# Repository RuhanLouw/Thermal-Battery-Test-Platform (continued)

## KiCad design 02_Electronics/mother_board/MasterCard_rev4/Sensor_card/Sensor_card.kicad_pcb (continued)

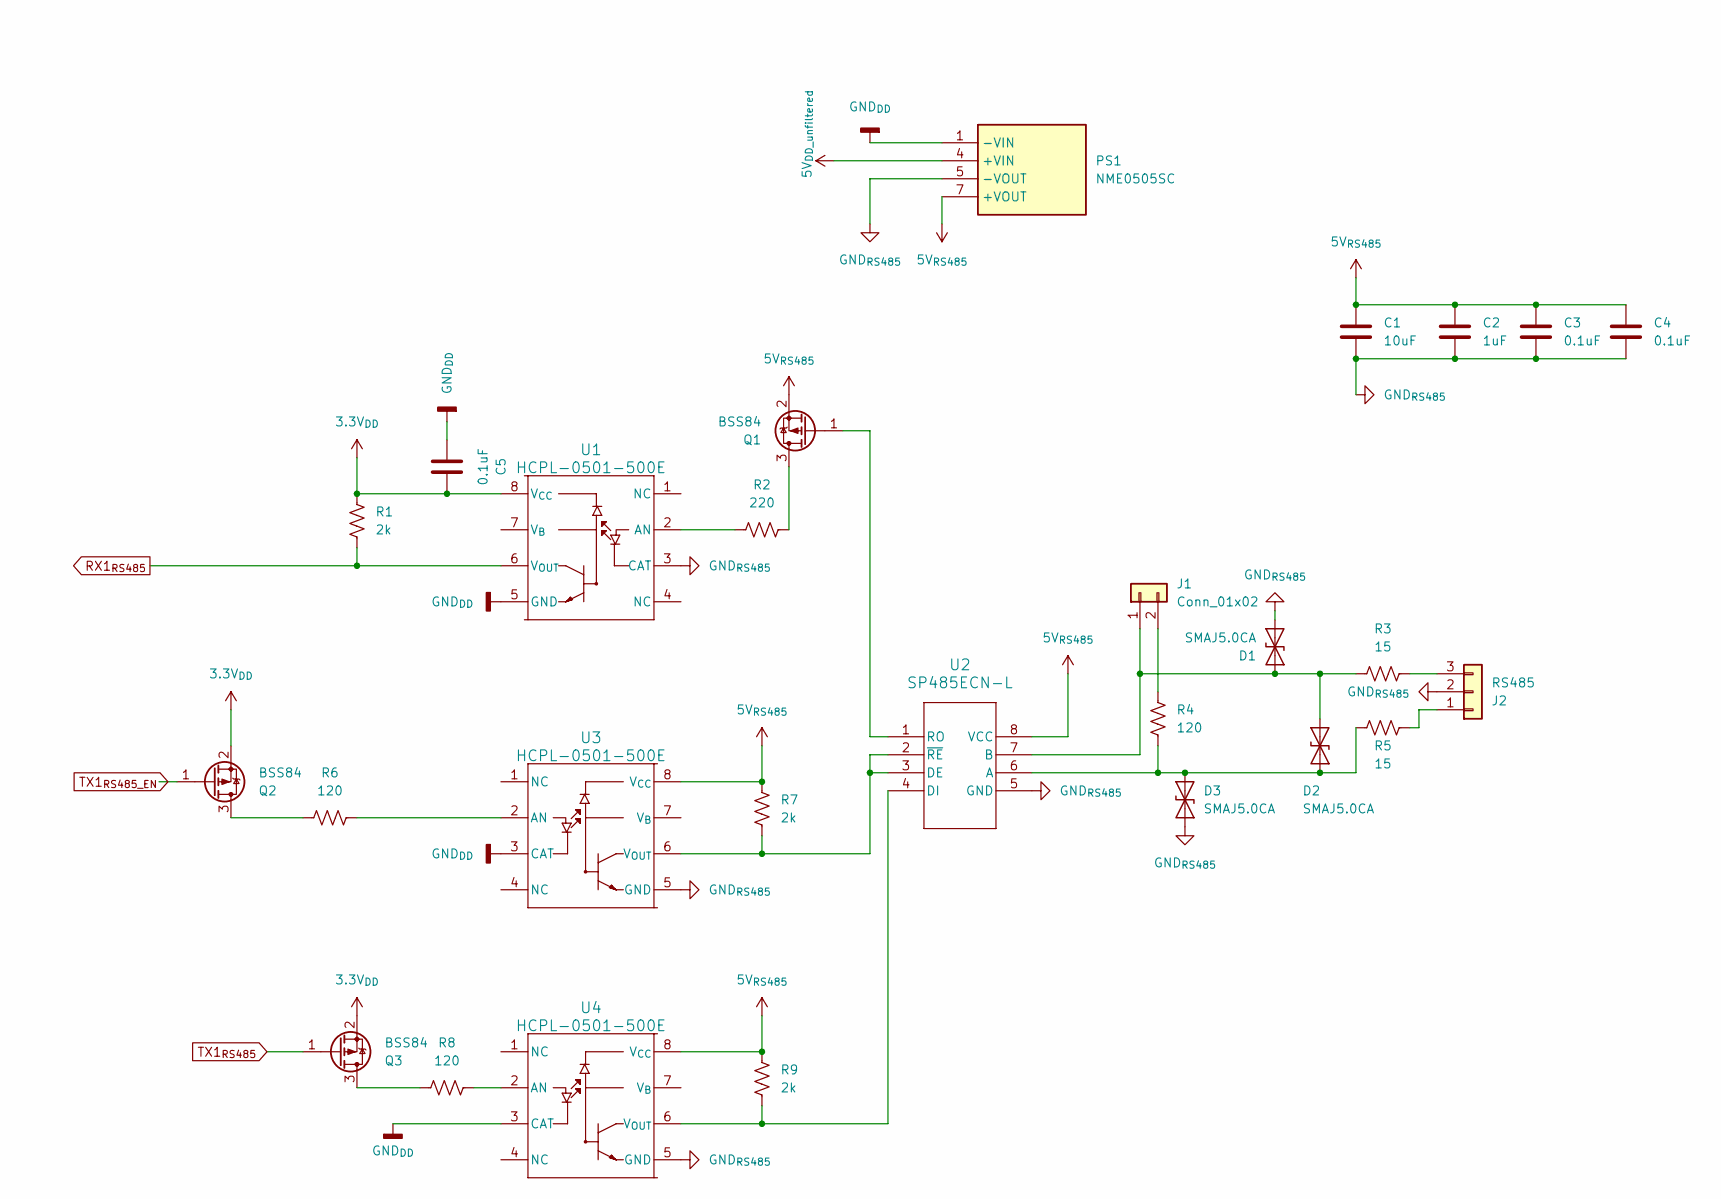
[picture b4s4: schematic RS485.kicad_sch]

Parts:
C1: 10uF; C_0805_2012Metric
C2: 1uF; C_0603_1608Metric
C3, C4, C5: 0.1uF; C_0603_1608Metric
D1, D2, D3: SMAJ5.0CA; D_SMA
J1: Conn_01x02; PinHeader_1x02_P2.54mm_Vertical
J2: RS485; TE_282857-3_screw
PS1: NME0505SC; Mouser Part Number 580-NME0505SC
Q1, Q2, Q3: BSS84; SOT-23
R1, R7, R9: 2k; R_0603_1608Metric
R2: 220; R_0603_1608Metric
R3, R5: 15; R_1206_3216Metric
R4, R6, R8: 120; R_0603_1608Metric
U1, U3, U4: HCPL-0501-500E; SO8_HCPL-0501-500_BRA
U2: SP485ECN-L; NSOIC-8

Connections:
3.3V_{DD}: C5.2, Q2.2 (S), Q3.2 (S), R1.2, U1.8 (V_{CC}); also elsewhere on the board
5V_{DD_unfiltered}: PS1.4 (+VIN); also elsewhere on the board
5V_{RS485}: C1.1, C2.1, C3.1, C4.1, PS1.7 (+VOUT), Q1.2 (S), R7.2, R9.2, U2.8 (VCC), U3.8 (V_{CC}), U4.8 (V_{CC})
GND_{DD}: C5.1, PS1.1 (-VIN), U1.5 (GND), U3.3 (CAT), U4.3 (CAT); also elsewhere on the board
GND_{RS485}: C1.2, C2.2, C3.2, C4.2, D1.1 (A1), D3.1 (A1), J2.2, PS1.5 (-VOUT), U1.3 (CAT), U2.5 (GND), U3.5 (GND), U4.5 (GND)
unnamed: D1.2 (A2), D2.1 (A1), J1.1, R3.1, U2.7 (B)
unnamed: D2.2 (A2), D3.2 (A2), R4.2, R5.1, U2.6 (A)
unnamed: J1.2, R4.1
unnamed: J2.1, R5.2
unnamed: J2.3, R3.2
unnamed: Q1.3 (D), R2.1
unnamed: Q1.1 (G), U2.1 (RO)
unnamed: Q2.3 (D), R6.1
unnamed: Q3.3 (D), R8.1
unnamed: R2.2, U1.2 (AN)
unnamed: R7.1, U2.2 (~RE), U2.3 (DE), U3.6 (V_{OUT})
unnamed: R9.1, U2.4 (DI), U4.6 (V_{OUT})
unnamed: R6.2, U3.2 (AN)
unnamed: R8.2, U4.2 (AN)
RX1_{RS485}: R1.1, U1.6 (V_{OUT}); also elsewhere on the board
TX1_{RS485_EN}: Q2.1 (G); also elsewhere on the board
TX1_{RS485}: Q3.1 (G); also elsewhere on the board

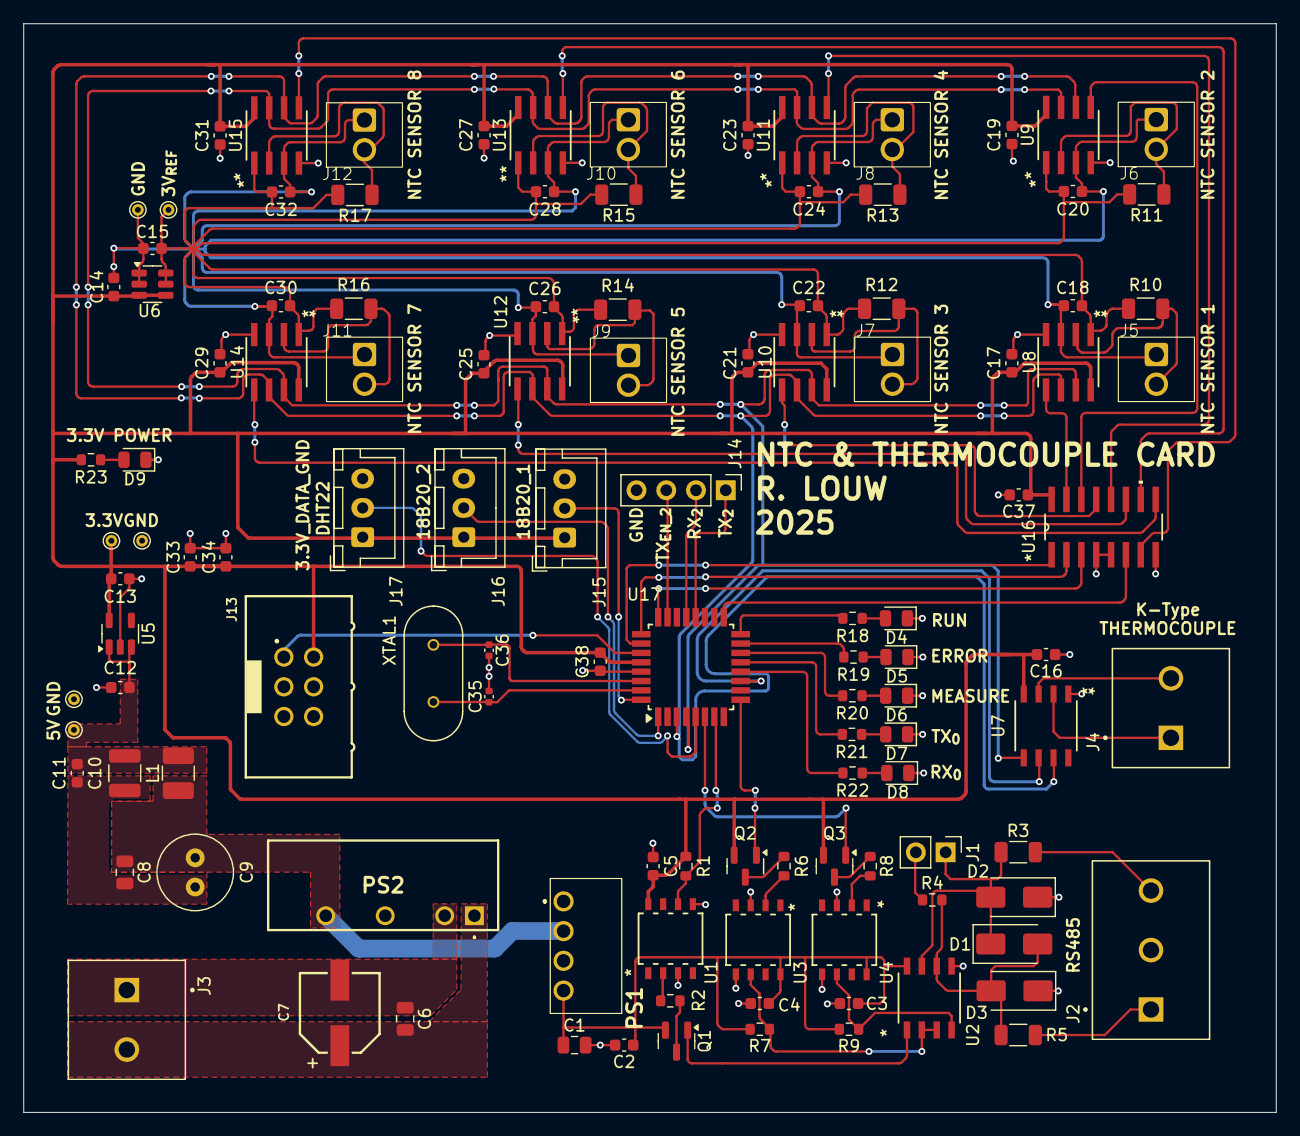
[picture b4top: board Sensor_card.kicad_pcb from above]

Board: 2 copper layers, 107.0 x 93.0 mm, 113 parts (1 on the bottom side), 88 nets.

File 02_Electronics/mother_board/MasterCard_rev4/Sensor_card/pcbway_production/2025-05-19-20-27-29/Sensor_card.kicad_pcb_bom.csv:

Designator,Quantity,Value,Footprint,Package,MPN,DNP,Mount_Type,Description,Sim.Pins,Height,Mouser Part Number,Mouser Price/Stock,Manufacturer_Name,PARTREV,STANDARD,MANUFACTURER
"C1, C6, C8",3,10uF,C_0805_2012Metric,,,,smt,10 µF ±10% 10V Ceramic Capacitor X7R 0805 (2012 Metric),,,,,,,,
C10,1,22uF,C_1210_3225Metric,,,,smt,CAP CER 22UF 16V X7R 1210,,,,,,,,
"C11, C14, C2, C33",4,1uF,C_0603_1608Metric,,,,smt,[C33]CAP CER 1UF 25V X7R 0603; [C2]CAP CER 1UF 10V X7R 0603,,,,,,,,
"C12, C13, C15",3,2.2uF,C_0603_1608Metric,,,,smt,CAP CER 2.2UF 25V X5R 0603,,,,,,,,
"C16, C17, C18, C19, C20, C21, C22, C23, C24, C25, C26, C27, C28, C29, C3, C30, C31, C32, C37, C38, C4, C5",22,0.1uF,C_0603_1608Metric,,,,smt,"[C37,C38]0.1 µF ±10% 50V Ceramic Capacitor X7R 0603 (1608 Metric); [C4,C5]Unpolarized capacitor",,,,,,,,
C34,1,10n,C_0603_1608Metric,,,,smt,Unpolarized capacitor,,,,,,,,
"C35, C36",2,18pF,C_0402_1005Metric,,,,smt,CAP CER 18PF 50V C0G/NP0 0402,,,,,,,,
C7,1,47uF,WCAP-ASLI_6.3X5.5_DXL_47uF,,,,smt,"47 µF 35 V Aluminum Electrolytic Capacitors Radial, Can - SMD 2000 Hrs @ 105°C",,,,,,,,
C9,1,100uF,C_Radial_D6.3mm_H11.0mm_P2.50mm,,,,tht,CAP ALUM 100UF 20% 35V RADIAL TH KEMET,,,,,,,,
"D1, D2, D3",3,SMAJ5.0CA,D_SMA,,,,smt,"400W bidirectional Transient Voltage Suppressor, 5.0Vr, SMA(DO-214AC)",,,,,,,,
"D4, D5, D6, D7, D8, D9",6,LED,LED_0805_2012Metric,,,,smt,LED GREEN CLEAR 0805 SMD,1=K 2=A,,,,,,,
J1,1,Conn_01x02,PinHeader_1x02_P2.54mm_Vertical,,,,tht,"Generic connector, single row, 01x02, script generated (kicad-library-utils/schlib/autogen/connector/)",,,,,,,,
"J10, J11, J12, J5, J6, J7, J8, J9",8,Screw_Terminal_01x02,TERM BLOCK 2P HORIZON 2.54MM PCB,,,,tht,"Generic screw terminal, single row, 01x02, script generated (kicad-library-utils/schlib/autogen/connector/)",,,,,,,,
J13,1,Conn_02x03_Top_Bottom,61200621621,,,,tht,"Generic connector, double row, 02x03, top/bottom pin numbering scheme (row 1: 1...pins_per_row, row2: pins_per_row+1 ... num_pins), script generated (kicad-library-utils/schlib/autogen/connector/)",,,,,,,,
J14,1,Conn_01x03,PinHeader_1x03_P2.54mm_Vertical,,,,tht,"Generic connector, single row, 01x03, script generated (kicad-library-utils/schlib/autogen/connector/)",,,,,,,,
"J15, J16, J17",3,Conn_01x03,JST_XH_B3B-XH-A_1x03_P2.50mm_Vertical,,,,tht,"Generic connector, single row, 01x03, script generated (kicad-library-utils/schlib/autogen/connector/)",,,,,,,,
J2,1,RS485,TE_282857-3_screw,,,,tht,"Generic connector, single row, 01x03, script generated (kicad-library-utils/schlib/autogen/connector/)",,,,,,,,
"J3, J4",2,Screw_Terminal_01x02,TE_282857-2_screw,,,,tht,"[J3]2 Position Wire to Board Terminal Block Horizontal with Board 0.200"" (5.08mm) Through Hole; [J4]Generic screw terminal, single row, 01x02, script generated (kicad-library-utils/schlib/autogen/connector/)",,,,,,,,
L1,1,4.7uH,L_1210_3225Metric_Pad1.42x2.65mm_HandSolder_cad,,,,smt,4.7 µH Unshielded Wirewound Inductor 800 mA 190mOhm Max 1210 (3225 Metric),,,,,,,,
PS1,1,NME0505SC,NME0505SC,,NME0505SC,,tht,"Murata Power Solutions NME 1W Isolated DC-DC Converter Through Hole, Vin 4.5  5.5 V dc, Vout 5V dc",,10.25,580-NME0505SC,https://www.mouser.co.uk/ProductDetail/Murata-Power-Solution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,Murata Electronics,,,
PS2,1,NMG1205SC,NMG1205SC,,,,tht,Isolated DC/DC Converters - Through Hole 2W TH 2W 12-5V SIP DC/DC,,,,,,,,
"Q1, Q2, Q3",3,BSS84,SOT-23,,,,smt,"-0.13A Id, -50V Vds, P-Channel MOSFET, SOT-23",,,,,,,,
"R1, R7, R9",3,2k,R_0603_1608Metric,,,,smt,"Resistor, US symbol",,,,,,,,
"R10, R11, R12, R13, R14, R15, R16, R17",8,10k,R_1206_3216Metric,,,,smt,"10 kOhms ±0.01% 0.25W, 1/4W Chip Resistor 1206 (3216 Metric) Automotive AEC-Q200 Thin Film",,,,,,,,
"R18, R19, R20, R21, R22, R23",6,75,R_0603_1608Metric,,,,smt,RES SMD 75 OHM 1% 1/10W 0603,,,,,,,,
R2,1,220,R_0603_1608Metric,,,,smt,"Resistor, US symbol",,,,,,,,
"R3, R5",2,15,R_1206_3216Metric,,,,smt,"Resistor, US symbol",,,,,,,,
"R4, R6, R8",3,120,R_0603_1608Metric,,,,smt,"Resistor, US symbol",,,,,,,,
"Star_Point1, Star_Point2",2,8,STARPOINT 9 ROUND PAD,,,,smt,,,,,,,,,
TIE1,1,~,Star_Point_3,,,,smt,,,,,,,,,
"U1, U3, U4",3,HCPL-0501-500E,SO8_HCPL-0501-500_BRA,,,,smt,,,,,,,,,
"U10, U11, U12, U13, U14, U15, U8, U9",8,MCP3201,SOIC8-N_MC_MCH,,,,smt,"2.7V 12-Bit A/D Converter with SPI™ Serial Interface, PDIP-8/SOIC-8/MSOP-8/TSSOP-8",,,,,,,,
U16,1,SN74HC138DR,SN74HC138DR,,,,smt,Decoder/Demultiplexer 1 x 3:8 16-SOIC,,,,,,,,
U17,1,AVR128DB32x-xPT,TQFP-32_7x7mm_P0.8mm,,,,smt,"24MHz, 128kB Flash, 16kB SRAM, EEPROM with Op Amps and Multi-Voltage I/O, TQFP-32",,,,,,,,
U2,1,SP485ECN-L,NSOIC-8,,,,smt,RS485,,,,,,,,
U5,1,LP5907MFX-3.3,SOT-23-5,,,,smt,"250-mA Ultra-Low-Noise Low-IQ LDO, 3.3V, SOT-23",,,,,,,,
U6,1,REF3430IDBVR,SOT-23-6,,,,smt,Series Voltage Reference IC Fixed 3V V ±0.05% 10 mA SOT-23-6,,,,,,,,
U7,1,MAX31855KASA+T,21-0041B_8_MXM,,,,smt,,,,,,,,,
XTAL1,1,ABL-16.000MHZ-B2,XTAL_HC49P488W46L1150T500H350,,,,tht,16 MHz ±20ppm Crystal 18pF 40 Ohms HC-49/US,,,,,,03.27.2018,IPC-7351B,Abracon

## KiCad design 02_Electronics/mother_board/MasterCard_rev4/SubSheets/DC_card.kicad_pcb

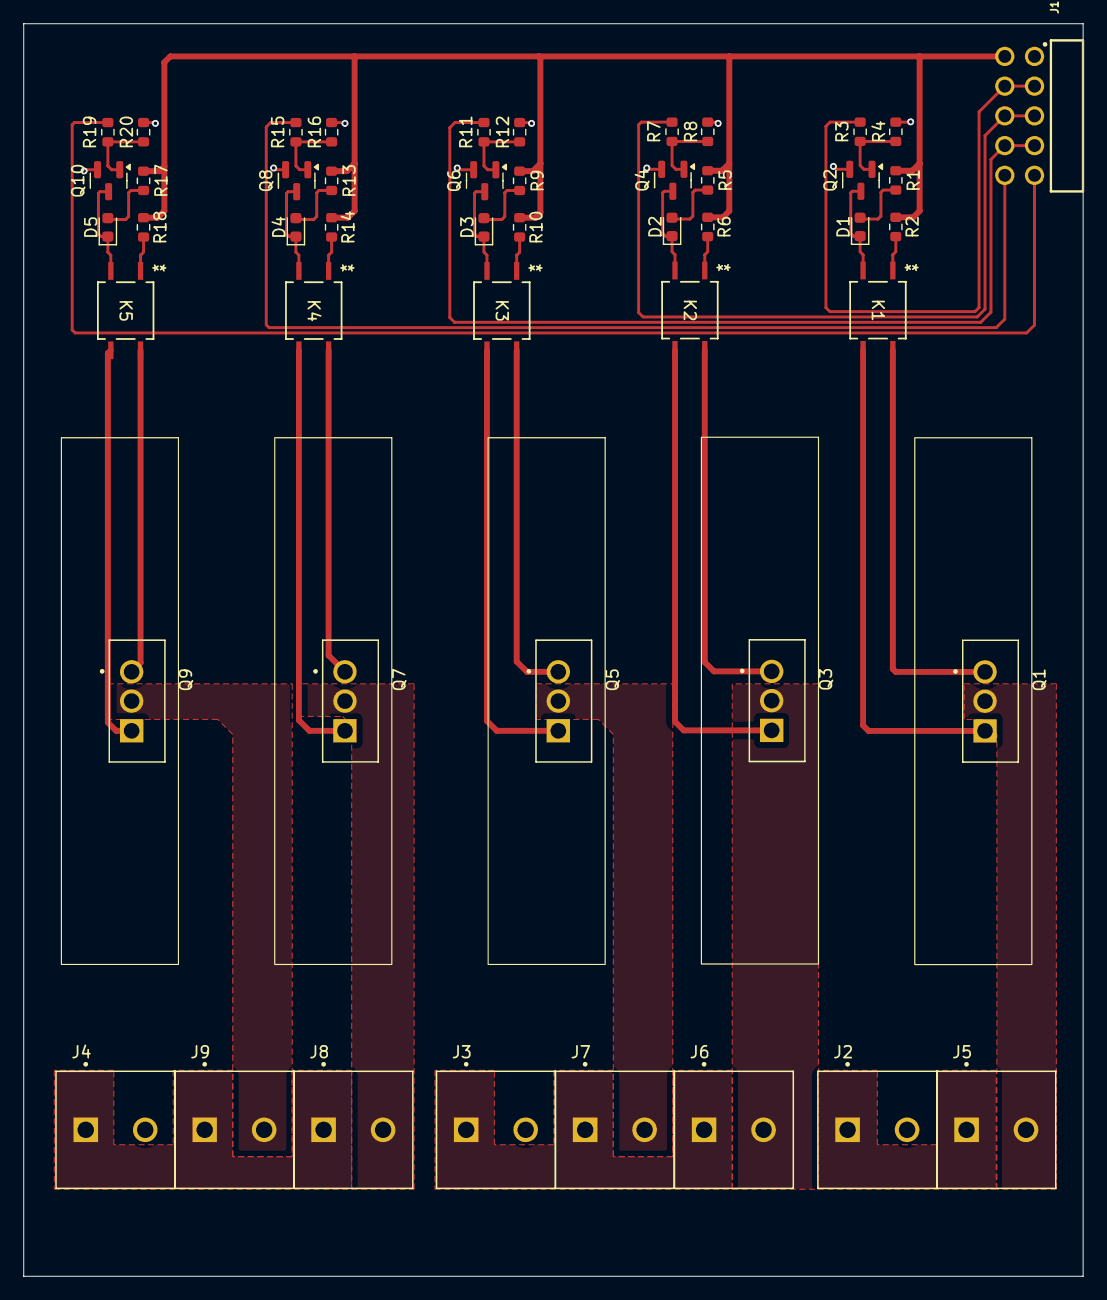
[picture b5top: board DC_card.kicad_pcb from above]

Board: 2 copper layers, 90.5 x 107.0 mm, 49 parts (0 on the bottom side), 43 nets.

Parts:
D1, D2, D3, D4, D5: LED; D_0603_1608Metric
J1: CONN HEADER R/A 10POS 2.54MM; CONN HEADER RA 10POS 2.54MM
J2, J3, J4: Own 12 Supply; TE_282857-2_screw
J5, J6, J7, J8, J9: DC_Compressor_MAIN; TE_282857-2_screw
K1, K2, K3, K4, K5: APV1121S; SOP4PIN_PAN-M
Q1, Q3, Q5, Q7, Q9: IRFB7545PBF; v2008b_IRFB7545PBF
Q2, Q4, Q6, Q8, Q10: BSS138L; SOT-23
R1, R5, R9, R13, R17: 142; R_0603_1608Metric
R2, R6, R10, R14, R18: 187; R_0603_1608Metric
R3, R7, R11, R15, R19: 300; R_0603_1608Metric
R4, R8, R12, R16, R20: 10k; R_0603_1608Metric

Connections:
5V_{DD}: J1.2, R1.2, R2.1, R5.2, R6.1, R9.2, R10.1, R13.2, R14.1, R17.2, R18.1
12V_{CC_comp}: J2.1, J5.1
12V_{CC_fans}: J4.1, J8.1, J9.1
12V_{CC_hbed}: J3.1, J6.1, J7.1
Compressor_MAIN: J1.3, J1.4, R3.1
Evaporator_FAN: J1.10, R15.1
GND_{CC_comp}: J2.2, K1.3, Q1.3 (S)
GND_{CC_fans}: J4.2, K4.3, K5.3, Q7.3 (S), Q9.3 (S)
GND_{CC_hbed}: J3.2, K2.3, K3.3, Q3.3 (S), Q5.3 (S)
GND_{DD}: J1.1, Q2.2 (S), Q4.2 (S), Q6.2 (S), Q8.2 (S), Q10.2 (S), R4.2, R8.2, R12.2, R16.2, R20.2
HeatBed_1: J1.5, J1.6, R7.1
HeatBed_2: J1.7, J1.8, R11.1
HeatBed_FAN: J1.9, R19.1
unnamed: D1.2 (A), R1.1
unnamed: D1.1 (K), K1.2, Q2.3 (D)
unnamed: D2.2 (A), R5.1
unnamed: D2.1 (K), K2.2, Q4.3 (D)
unnamed: D3.2 (A), R9.1
unnamed: D3.1 (K), K3.2, Q6.3 (D)
unnamed: D4.2 (A), R13.1
unnamed: D4.1 (K), K4.2, Q8.3 (D)
unnamed: D5.2 (A), R17.1
unnamed: D5.1 (K), K5.2, Q10.3 (D)
unnamed: J5.2, Q1.1 (D)
unnamed: J6.2, Q3.1 (D)
unnamed: J7.2, Q5.1 (D)
unnamed: J8.2, Q7.1 (D)
unnamed: J9.2, Q9.1 (D)
unnamed: K1.1, R2.2
unnamed: K2.1, R6.2
unnamed: K3.1, R10.2
unnamed: K4.1, R14.2
unnamed: K5.1, R18.2
unnamed: K1.4, Q1.2 (G)
unnamed: Q2.1 (G), R3.2, R4.1
unnamed: K2.4, Q3.2 (G)
unnamed: Q4.1 (G), R7.2, R8.1
unnamed: K3.4, Q5.2 (G)
unnamed: Q6.1 (G), R11.2, R12.1
unnamed: K4.4, Q7.2 (G)
unnamed: Q8.1 (G), R15.2, R16.1
unnamed: K5.4, Q9.2 (G)
unnamed: Q10.1 (G), R19.2, R20.1

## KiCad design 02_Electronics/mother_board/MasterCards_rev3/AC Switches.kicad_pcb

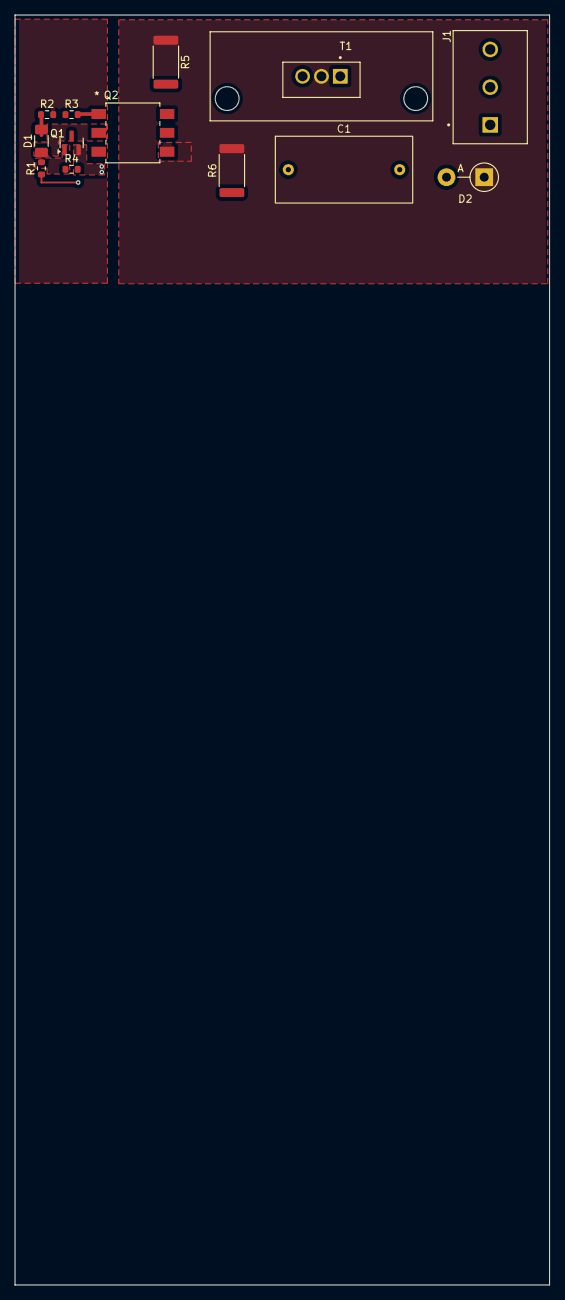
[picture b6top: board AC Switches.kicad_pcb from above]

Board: 2 copper layers, 72.0 x 171.1 mm, 13 parts (0 on the bottom side), 11 nets.

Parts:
C1: 0.1u; CAP FILM 0.22UF 10 800VDC RAD
D1: LED; R_1206_3216Metric_Pad1.30x1.75mm_HandSolder
D2: P6KE400CA; D_DO-15_P5.08mm_Vertical_AnodeUp
J1: AC_sw; TE_282857-3_screw
Q1: BSS138L; SOT-23
Q2: MOC3063S-TA1; MOC306XS_LTO
R1: 300; R_0603_1608Metric
R2: 142; R_0603_1608Metric
R3: 10k; R_0603_1608Metric
R4: 187; R_0603_1608Metric
R5: 620; R_2512_6332Metric
R6: 100; R_2512_6332Metric
T1: BTA316-800E,127; TO254P1040X475X1935-3__U_heat

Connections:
5V_{DD}: R2.2, R4.1
230AC: D2.1 (A1), R5.1, R6.2, T1.2
GND_{DD}: Q1.2 (S), R3.2
unnamed: C1.1, R6.1
unnamed: D1.2 (A), R2.1
unnamed: D1.1 (K), Q1.3 (D), Q2.2
unnamed: C1.2, D2.2 (A2), J1.1, T1.1
unnamed: Q1.1 (G), R1.2, R3.1
unnamed: Q2.1, R4.2
unnamed: Q2.4, T1.3
unnamed: Q2.6, R5.2
